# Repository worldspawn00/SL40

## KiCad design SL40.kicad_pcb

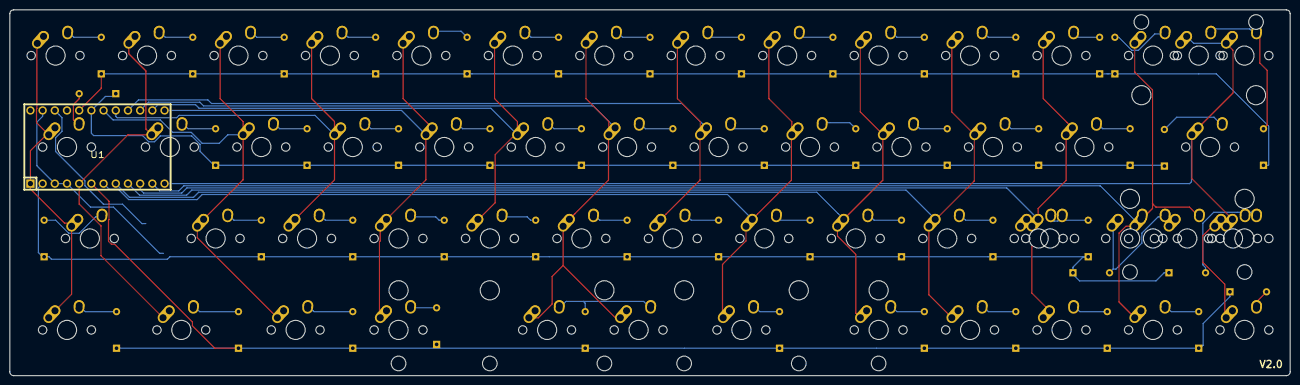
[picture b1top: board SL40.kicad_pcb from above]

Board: 2 copper layers, 266.7 x 76.2 mm, 110 parts (1 on the bottom side), 68 nets.

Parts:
 : 2.25U; MX-2.25U-ReversedStabilizers-NoLED
 #2: 2.25U; MX-2.25U-ReversedStabilizers-NoLED
 #3,  #4,  #7,  #8: 1U; MX-1U-NoLED
 #5: 1.25U; MX-1.25U-NoLED
 #6: 2U; MX-2U-ReversedStabilizers-NoLED
 #9: 2U; MX-2U-NoLED
D1, D1#2, D1#3, D1#4, D2, D3, D4, D5, D6, D7, D8, D9, D10, D11, D12, D13, D14, D15, D16, D17, D18, D19, D20, D21, D22, D23, D24, D25, D26, D27, D28, D29, D30, D31, D32, D33, D34, D35, D36, D37, D38, D39, D40, D41, D42, D43, D44, D45, D46, D47, D48: D_small; ComboDiode
MX1, MX2, MX3, MX4, MX5, MX6, MX7, MX8, MX9, MX10, MX11, MX12, MX13, MX14, MX16, MX17, MX18, MX19, MX20, MX21, MX22, MX23, MX24, MX25, MX26, MX29, MX30, MX31, MX32, MX33, MX34, MX35, MX36, MX37, MX39, MX40, MX45, MX46, MX47, MX48: MX-1U; MX-1U-NoLED
MX15, MX38, MX41, MX42, MX43: MX-1.25U; MX-1.25U-NoLED
MX27, MX28: MX-1.75U; MX-1.75U-NoLED
MX44: MX-6.25U; MX-6.25U-ReversedStabilizers-NoLED
SW1: SW_Push; SKQG-1155865
U1: Arduino Pro Micro; ARDUINO_PRO_MICRO

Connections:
COL0: MX1.1, MX15.1, MX28.1, MX41.1, U1.1
COL1: MX2.1, MX16.1, MX42.1, U1.5
COL2: MX3.1, MX17.1, MX29.1, MX43.1, U1.18
COL3: MX4.1, MX18.1, MX30.1, U1.17
COL4: #7.1, MX5.1, MX19.1, MX31.1, U1.13
COL5: MX6.1, MX20.1, MX32.1, U1.14
COL6: .1, MX7.1, MX21.1, MX33.1, MX44.1, U1.15
COL7: MX8.1, MX22.1, MX34.1, U1.16
COL8: #6.1, MX9.1, MX23.1, MX35.1, U1.7
COL9: #8.1, MX10.1, MX24.1, MX36.1, U1.8
COL10: MX11.1, MX25.1, MX37.1, MX45.1, U1.9
COL11: MX12.1, MX26.1, MX38.1, MX46.1, U1.10
COL12: #2.2, MX13.1, MX39.1, MX47.1, U1.11
COL13: #5.1, #9.1, MX14.1, MX27.1, MX40.1, MX48.1, U1.12
GND: SW1.1, U1.3, U1.4, U1.23
unnamed: D1#4.2, MX1.2
unnamed: D2.2, MX2.2
unnamed: D3.2, MX3.2
unnamed: D4.2, MX4.2
unnamed: D5.2, MX5.2
unnamed: D6.2, MX6.2
unnamed: D7.2, MX7.2
unnamed: D8.2, MX8.2
unnamed: D9.2, MX9.2
unnamed: D10.2, MX10.2
unnamed: D11.2, MX11.2
unnamed: D12.2, MX12.2
unnamed: D13.2, MX13.2
unnamed: #9.2, D14.2, MX14.2
unnamed: D15.2, MX15.2
unnamed: D16.2, MX16.2
unnamed: D17.2, MX17.2
unnamed: D18.2, MX18.2
unnamed: D19.2, MX19.2
unnamed: D20.2, MX20.2
unnamed: D21.2, MX21.2
unnamed: D22.2, MX22.2
unnamed: D23.2, MX23.2
unnamed: D24.2, MX24.2
unnamed: D25.2, MX25.2
unnamed: D26.2, MX26.2
unnamed: D27.2, MX27.2
unnamed: D28.2, MX28.2
unnamed: D29.2, MX29.2
unnamed: D30.2, MX30.2
unnamed: D31.2, MX31.2
unnamed: D32.2, MX32.2
unnamed: D33.2, MX33.2
unnamed: D34.2, MX34.2
unnamed: D35.2, MX35.2
unnamed: D36.2, MX36.2
unnamed: D37.2, MX37.2
unnamed: #3.2, D38.2, MX38.2
unnamed: #4.1, D39.2, MX39.2
unnamed: D40.2, MX40.2
unnamed: D41.2, MX41.2
unnamed: D42.2, MX42.2
unnamed: D43.2, MX43.2
unnamed: .2, D44.2, MX44.2
unnamed: D45.2, MX45.2
unnamed: D46.2, MX46.2
unnamed: D47.2, MX47.2
unnamed: D48.2, MX48.2
unnamed: SW1.2, U1.22
ROW0: D1#4.1, D2.1, D3.1, D4.1, D5.1, D6.1, D7.1, D8.1, D9.1, D10.1, D11.1, D12.1, D13.1, D14.1, U1.20
ROW1: D15.1, D16.1, D17.1, D18.1, D19.1, D20.1, D21.1, D22.1, D23.1, D24.1, D25.1, D26.1, D27.1, U1.19
ROW2: D28.1, D29.1, D30.1, D31.1, D32.1, D33.1, D34.1, D35.1, D36.1, D37.1, D38.1, D39.1, D40.1, U1.2
ROW3: D41.1, D42.1, D43.1, D44.1, D45.1, D46.1, D47.1, D48.1, U1.6

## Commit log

2019-05-05 fixing names
2019-05-12 added firmware
2019-05-19 fixinf firmware
2019-05-21 fixing footprint
2019-06-11 new kicad version
2020-02-17 adding new layouts
2020-02-17 updating spacebars
2020-02-22 fixed issue with resistor footprint
